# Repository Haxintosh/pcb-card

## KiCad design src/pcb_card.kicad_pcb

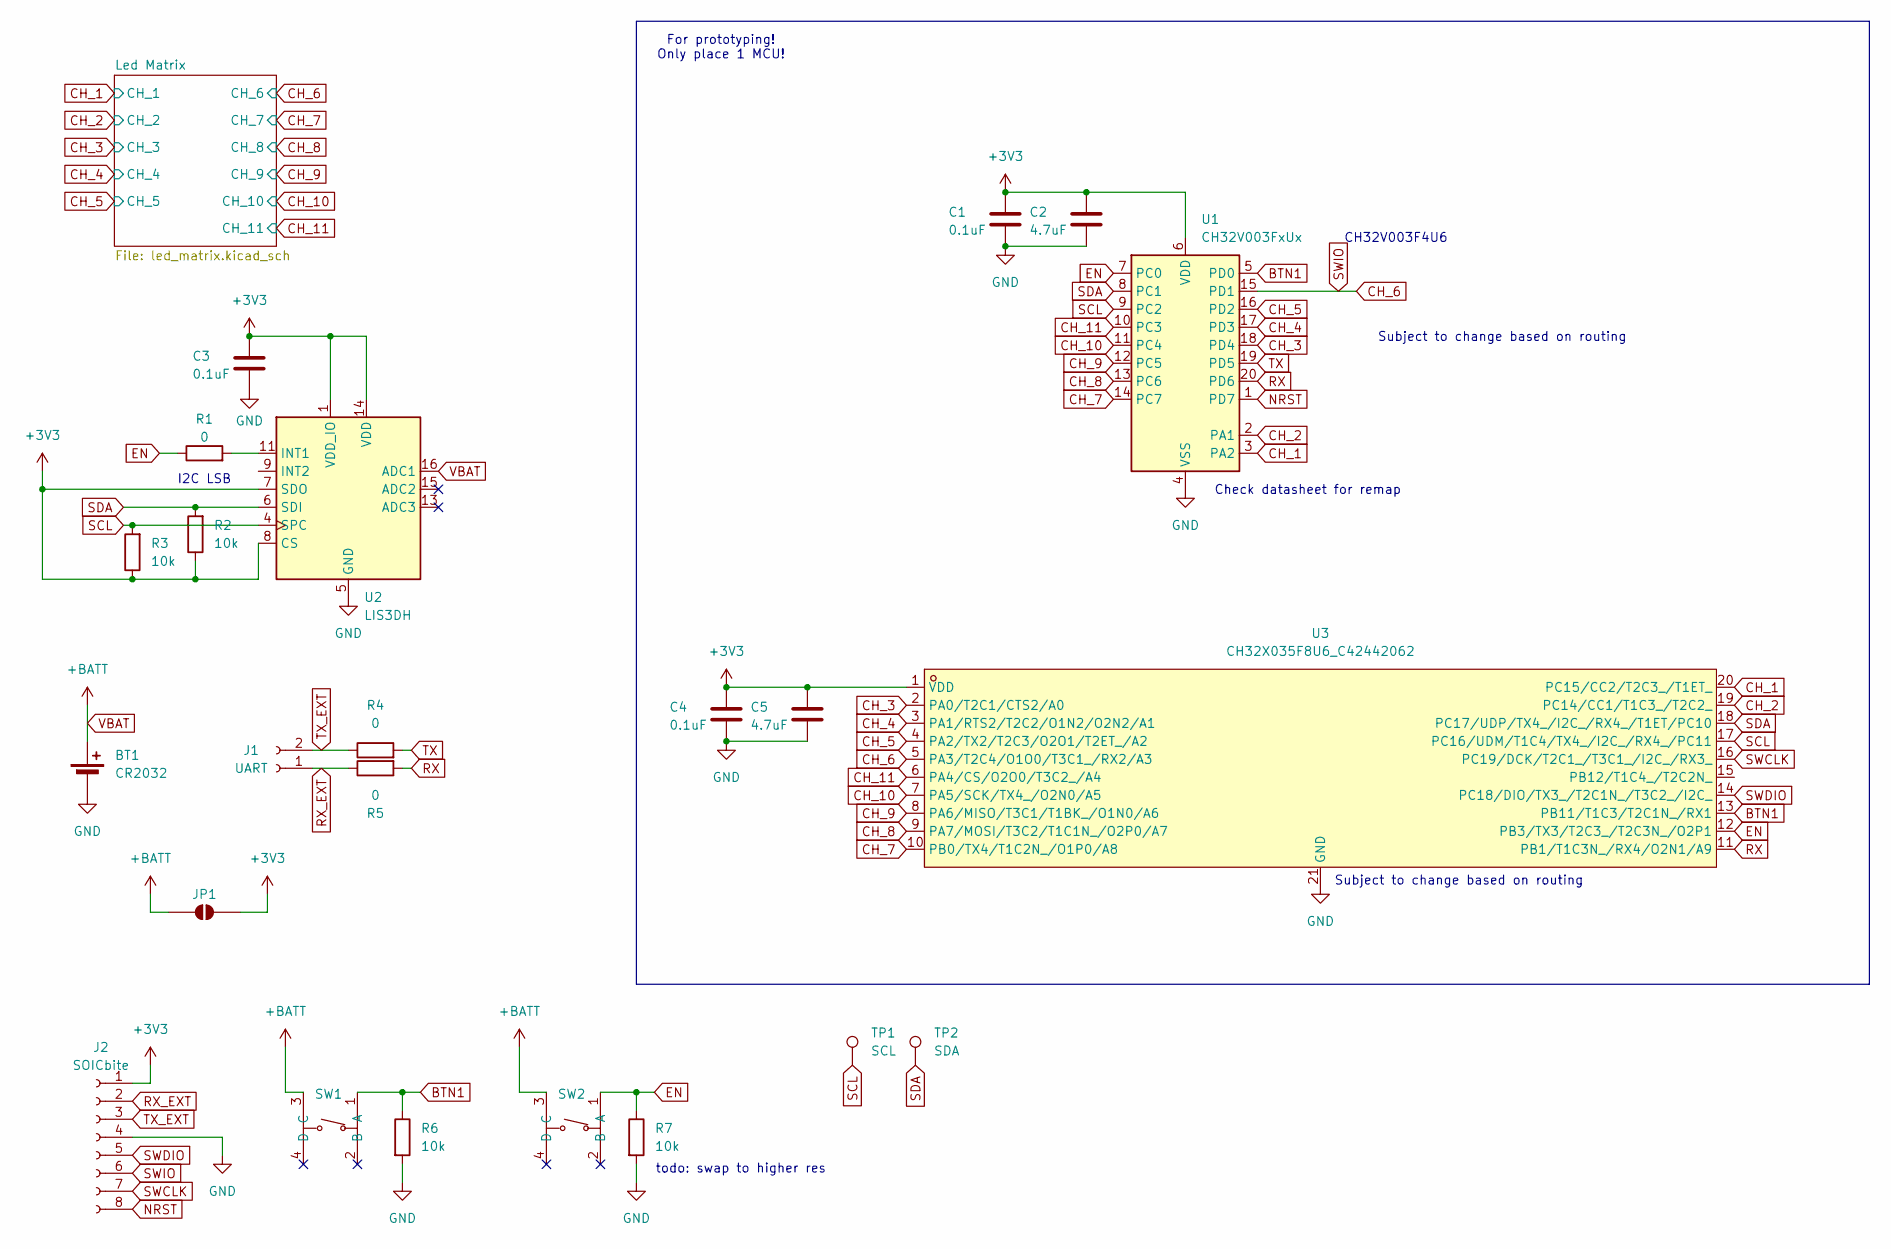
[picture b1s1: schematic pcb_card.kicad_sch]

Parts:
BT1: CR2032; BAT-TH_CR2032-BS-6-1
C1, C3, C4: 0.1uF; C_0603_1608Metric
C2, C5: 4.7uF; C_0603_1608Metric
J1: UART; JST_PH_B2B-PH-K_1x02_P2.00mm_Vertical
J2: SOICbite; SOIC_clipProgSmall
JP1: SolderJumper_2_Open; SolderJumper-2_P1.3mm_Open_TrianglePad1.0x1.5mm
R1, R4, R5: 0; R_0805_2012Metric_Pad1.20x1.40mm_HandSolder
R2, R3, R6, R7: 10k; R_0603_1608Metric
SW1, SW2: TS-1187A-B-A-B; SW-SMD_4P-L5.1-W5.1-P3.70-LS6.5-TL_H1.5; MPN TS-1187A-B-A-B; LCSC Part C318884
TP1: SCL; TestPoint_Pad_D2.0mm
TP2: SDA; TestPoint_Pad_D2.0mm
U1: CH32V003FxUx; QFN-20-1EP_3x3mm_P0.4mm_EP1.65x1.65mm; LCSC C5299908
U2: LIS3DH; LGA-16_3x3mm_P0.5mm_LayoutBorder3x5y
U3: CH32X035F8U6_C42442062; QFN-20-1EP_3x3mm_P0.4mm_EP1.65x1.65mm; MPN CH32X035F8U6; LCSC C42442062

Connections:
+3V3: C1.1, C2.1, C3.1, C4.1, C5.1, J2.1, JP1.2 (B), R2.1, R3.1, U1.6 (VDD), U2.1 (VDD_IO), U2.7 (SDO), U2.8 (CS), U2.14 (VDD), U3.1 (VDD)
BTN1: R6.1, SW1.1 (A), U1.5 (PD0), U3.13 (PB11/T1C3/T2C1N_/RX1)
CH_1: U1.3 (PA2), U3.20 (PC15/CC2/T2C3_/T1ET_); also elsewhere on the board
CH_2: U1.2 (PA1), U3.19 (PC14/CC1/T1C3_/T2C2_); also elsewhere on the board
CH_3: U1.18 (PD4), U3.2 (PA0/T2C1/CTS2/A0); also elsewhere on the board
CH_4: U1.17 (PD3), U3.3 (PA1/RTS2/T2C2/O1N2/O2N2/A1); also elsewhere on the board
CH_5: U1.16 (PD2), U3.4 (PA2/TX2/T2C3/O2O1/T2ET_/A2); also elsewhere on the board
CH_6: J2.6, U1.15 (PD1), U3.5 (PA3/T2C4/O1O0/T3C1_/RX2/A3); also elsewhere on the board
CH_7: U1.14 (PC7), U3.10 (PB0/TX4/T1C2N_/O1P0/A8); also elsewhere on the board
CH_8: U1.13 (PC6), U3.9 (PA7/MOSI/T3C2/T1C1N_/O2P0/A7); also elsewhere on the board
CH_9: U1.12 (PC5), U3.8 (PA6/MISO/T3C1/T1BK_/O1N0/A6); also elsewhere on the board
CH_10: U1.11 (PC4), U3.7 (PA5/SCK/TX4_/O2N0/A5); also elsewhere on the board
CH_11: U1.10 (PC3), U3.6 (PA4/CS/O2O0/T3C2_/A4); also elsewhere on the board
EN: R1.1, R7.1, SW2.1 (A), U1.7 (PC0), U3.12 (PB3/TX3/T2C3_/T2C3N_/O2P1)
GND: BT1.2 (-), C1.2, C2.2, C3.2, C4.2, C5.2, J2.4, R6.2, R7.2, U1.4 (VSS), U1.21 (VSS), U2.5 (GND), U2.10 (GND), U2.12 (GND), U3.21 (GND)
NRST: J2.8, U1.1 (PD7)
unnamed: R1.2, U2.11 (INT1)
RX: R5.2, U1.20 (PD6), U3.11 (PB1/T1C3N_/RX4/O2N1/A9)
RX_EXT: J1.1, J2.2, R5.1
SCL: R3.2, TP1.1 (1_1), U1.9 (PC2), U2.4 (SPC), U3.17 (PC16/UDM/T1C4/TX4_/I2C_/RX4_/PC11)
SDA: R2.2, TP2.1 (1_1), U1.8 (PC1), U2.6 (SDI), U3.18 (PC17/UDP/TX4_/I2C_/RX4_/T1ET/PC10)
SWCLK: J2.7, U3.16 (PC19/DCK/T2C1_/T3C1_/I2C_/RX3_)
SWDIO: J2.5, U3.14 (PC18/DIO/TX3_/T2C1N_/T3C2_/I2C_)
TX: R4.2, U1.19 (PD5)
TX_EXT: J1.2, J2.3, R4.1
VBAT: BT1.1 (+), JP1.1 (A), SW1.3 (C), SW2.3 (C), U2.16 (ADC1)

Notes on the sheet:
todo: swap to higher res
For prototyping! Only place 1 MCU!
Check datasheet for remap
Subject to change based on routing
CH32V003F4U6
I2C LSB

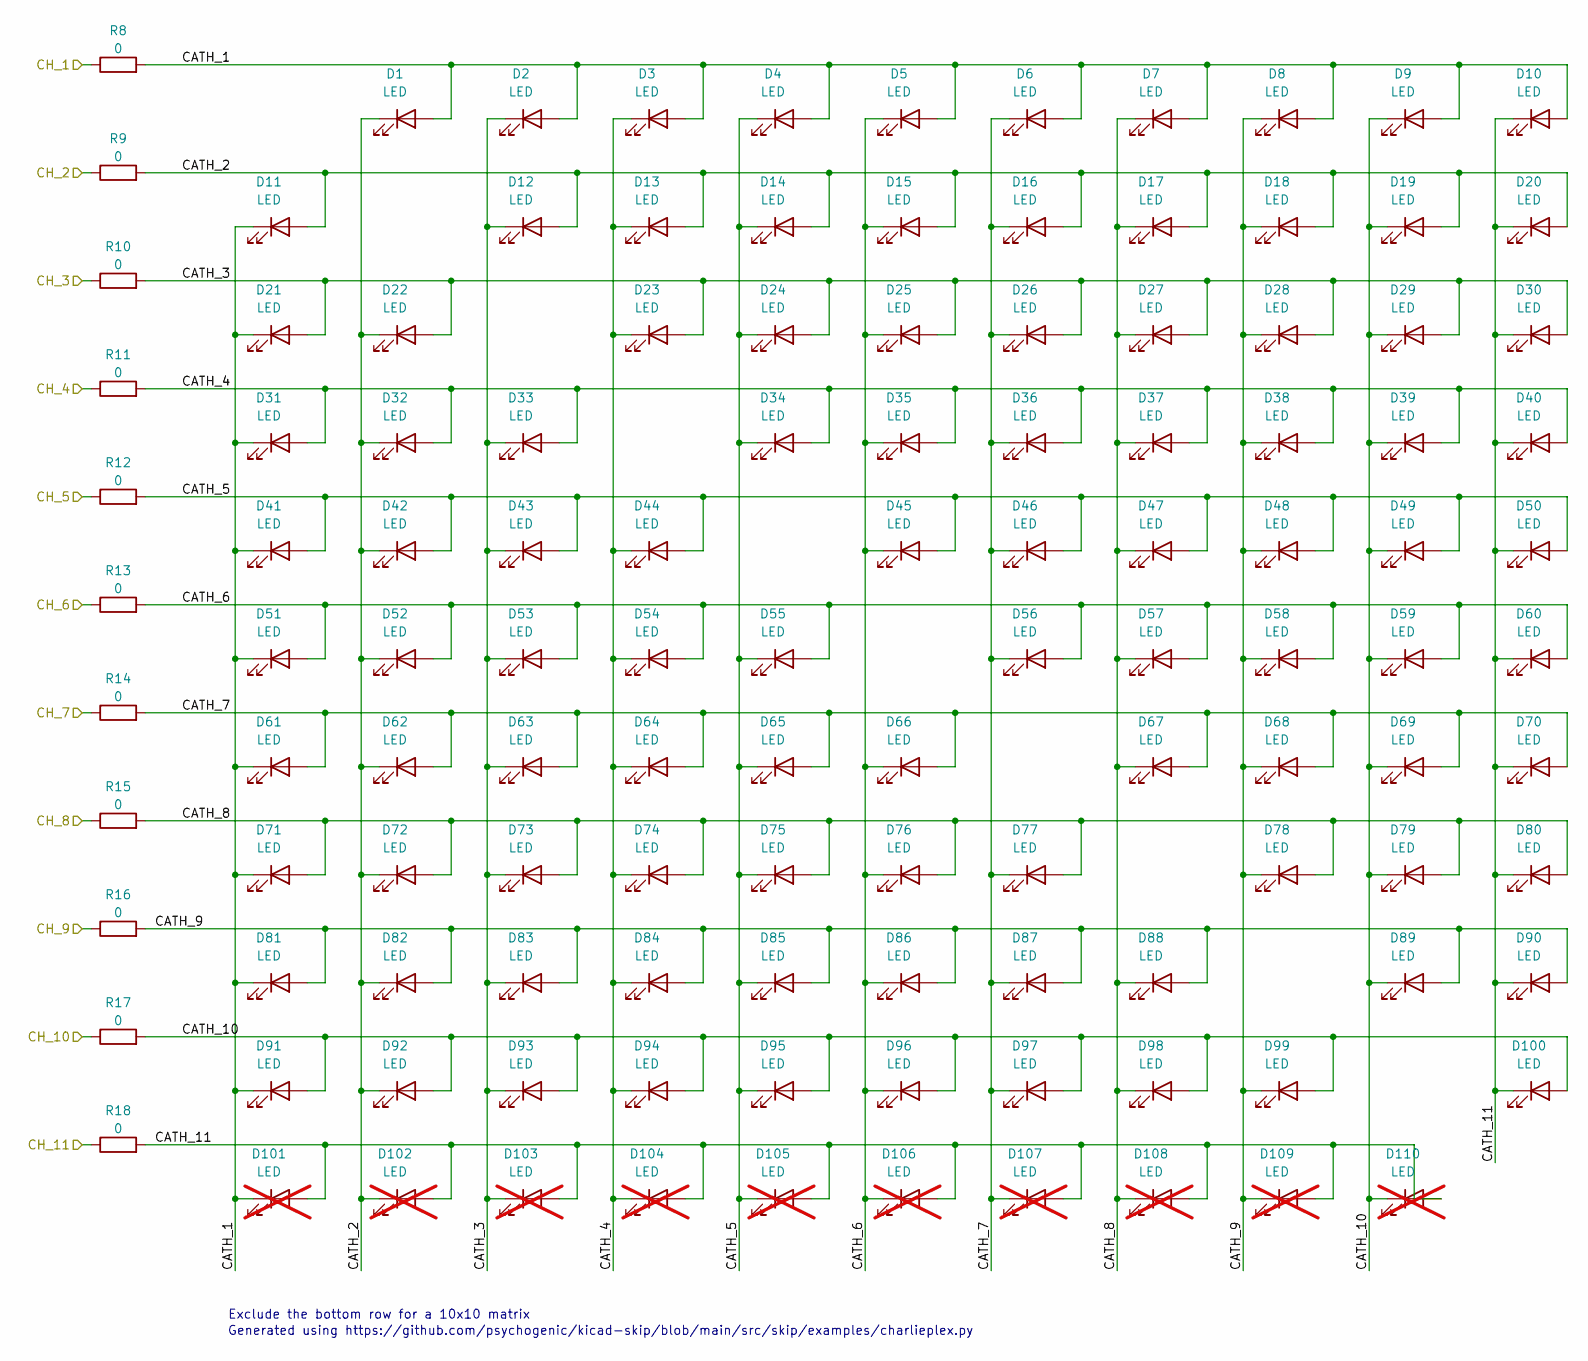
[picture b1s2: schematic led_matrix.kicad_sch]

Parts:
D1, D2, D3, D4, D5, D6, D7, D8, D9, D10, D11, D12, D13, D14, D15, D16, D17, D18, D19, D20, D21, D22, D23, D24, D25, D26, D27, D28, D29, D30, D31, D32, D33, D34, D35, D36, D37, D38, D39, D40, D41, D42, D43, D44, D45, D46, D47, D48, D49, D50, D51, D52, D53, D54, D55, D56, D57, D58, D59, D60, D61, D62, D63, D64, D65, D66, D67, D68, D69, D70, D71, D72, D73, D74, D75, D76, D77, D78, D79, D80, D81, D82, D83, D84, D85, D86, D87, D88, D89, D90, D91, D92, D93, D94, D95, D96, D97, D98, D99, D100: LED; LED_0603_1608Metric
D101, D102, D103, D104, D105, D106, D107, D108, D109, D110: LED; not fitted
R8, R9, R10, R11, R12, R13, R14, R15, R16, R17, R18: 0; R_0805_2012Metric_Pad1.20x1.40mm_HandSolder

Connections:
/Led Matrix/CATH_1: D1.2 (A), D2.2 (A), D3.2 (A), D4.2 (A), D5.2 (A), D6.2 (A), D7.2 (A), D8.2 (A), D9.2 (A), D10.2 (A), D11.1 (K), D21.1 (K), D31.1 (K), D41.1 (K), D51.1 (K), D61.1 (K), D71.1 (K), D81.1 (K), D91.1 (K), D101.1 (K), R8.2
/Led Matrix/CATH_2: D1.1 (K), D11.2 (A), D12.2 (A), D13.2 (A), D14.2 (A), D15.2 (A), D16.2 (A), D17.2 (A), D18.2 (A), D19.2 (A), D20.2 (A), D22.1 (K), D32.1 (K), D42.1 (K), D52.1 (K), D62.1 (K), D72.1 (K), D82.1 (K), D92.1 (K), D102.1 (K), R9.2
/Led Matrix/CATH_3: D2.1 (K), D12.1 (K), D21.2 (A), D22.2 (A), D23.2 (A), D24.2 (A), D25.2 (A), D26.2 (A), D27.2 (A), D28.2 (A), D29.2 (A), D30.2 (A), D33.1 (K), D43.1 (K), D53.1 (K), D63.1 (K), D73.1 (K), D83.1 (K), D93.1 (K), D103.1 (K), R10.2
/Led Matrix/CATH_4: D3.1 (K), D13.1 (K), D23.1 (K), D31.2 (A), D32.2 (A), D33.2 (A), D34.2 (A), D35.2 (A), D36.2 (A), D37.2 (A), D38.2 (A), D39.2 (A), D40.2 (A), D44.1 (K), D54.1 (K), D64.1 (K), D74.1 (K), D84.1 (K), D94.1 (K), D104.1 (K), R11.2
/Led Matrix/CATH_5: D4.1 (K), D14.1 (K), D24.1 (K), D34.1 (K), D41.2 (A), D42.2 (A), D43.2 (A), D44.2 (A), D45.2 (A), D46.2 (A), D47.2 (A), D48.2 (A), D49.2 (A), D50.2 (A), D55.1 (K), D65.1 (K), D75.1 (K), D85.1 (K), D95.1 (K), D105.1 (K), R12.2
/Led Matrix/CATH_6: D5.1 (K), D15.1 (K), D25.1 (K), D35.1 (K), D45.1 (K), D51.2 (A), D52.2 (A), D53.2 (A), D54.2 (A), D55.2 (A), D56.2 (A), D57.2 (A), D58.2 (A), D59.2 (A), D60.2 (A), D66.1 (K), D76.1 (K), D86.1 (K), D96.1 (K), D106.1 (K), R13.2
/Led Matrix/CATH_7: D6.1 (K), D16.1 (K), D26.1 (K), D36.1 (K), D46.1 (K), D56.1 (K), D61.2 (A), D62.2 (A), D63.2 (A), D64.2 (A), D65.2 (A), D66.2 (A), D67.2 (A), D68.2 (A), D69.2 (A), D70.2 (A), D77.1 (K), D87.1 (K), D97.1 (K), D107.1 (K), R14.2
/Led Matrix/CATH_8: D7.1 (K), D17.1 (K), D27.1 (K), D37.1 (K), D47.1 (K), D57.1 (K), D67.1 (K), D71.2 (A), D72.2 (A), D73.2 (A), D74.2 (A), D75.2 (A), D76.2 (A), D77.2 (A), D78.2 (A), D79.2 (A), D80.2 (A), D88.1 (K), D98.1 (K), D108.1 (K), R15.2
/Led Matrix/CATH_9: D8.1 (K), D18.1 (K), D28.1 (K), D38.1 (K), D48.1 (K), D58.1 (K), D68.1 (K), D78.1 (K), D81.2 (A), D82.2 (A), D83.2 (A), D84.2 (A), D85.2 (A), D86.2 (A), D87.2 (A), D88.2 (A), D89.2 (A), D90.2 (A), D99.1 (K), D109.1 (K), R16.2
/Led Matrix/CATH_10: D9.1 (K), D19.1 (K), D29.1 (K), D39.1 (K), D49.1 (K), D59.1 (K), D69.1 (K), D79.1 (K), D89.1 (K), D91.2 (A), D92.2 (A), D93.2 (A), D94.2 (A), D95.2 (A), D96.2 (A), D97.2 (A), D98.2 (A), D99.2 (A), D100.2 (A), D110.1 (K), R17.2
/Led Matrix/CATH_11: D10.1 (K), D20.1 (K), D30.1 (K), D40.1 (K), D50.1 (K), D60.1 (K), D70.1 (K), D80.1 (K), D90.1 (K), D100.1 (K), D101.2 (A), D102.2 (A), D103.2 (A), D104.2 (A), D105.2 (A), D106.2 (A), D107.2 (A), D108.2 (A), D109.2 (A), D110.2 (A), R18.2
CH_1: R8.1; also elsewhere on the board
CH_2: R9.1; also elsewhere on the board
CH_3: R10.1; also elsewhere on the board
CH_4: R11.1; also elsewhere on the board
CH_5: R12.1; also elsewhere on the board
CH_6: R13.1; also elsewhere on the board
CH_7: R14.1; also elsewhere on the board
CH_8: R15.1; also elsewhere on the board
CH_9: R16.1; also elsewhere on the board
CH_10: R17.1; also elsewhere on the board
CH_11: R18.1; also elsewhere on the board

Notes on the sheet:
Generated using https://github.com/psychogenic/kicad-skip/blob/main/src/skip/examples/charlieplex.py
Exclude the bottom row for a 10x10 matrix

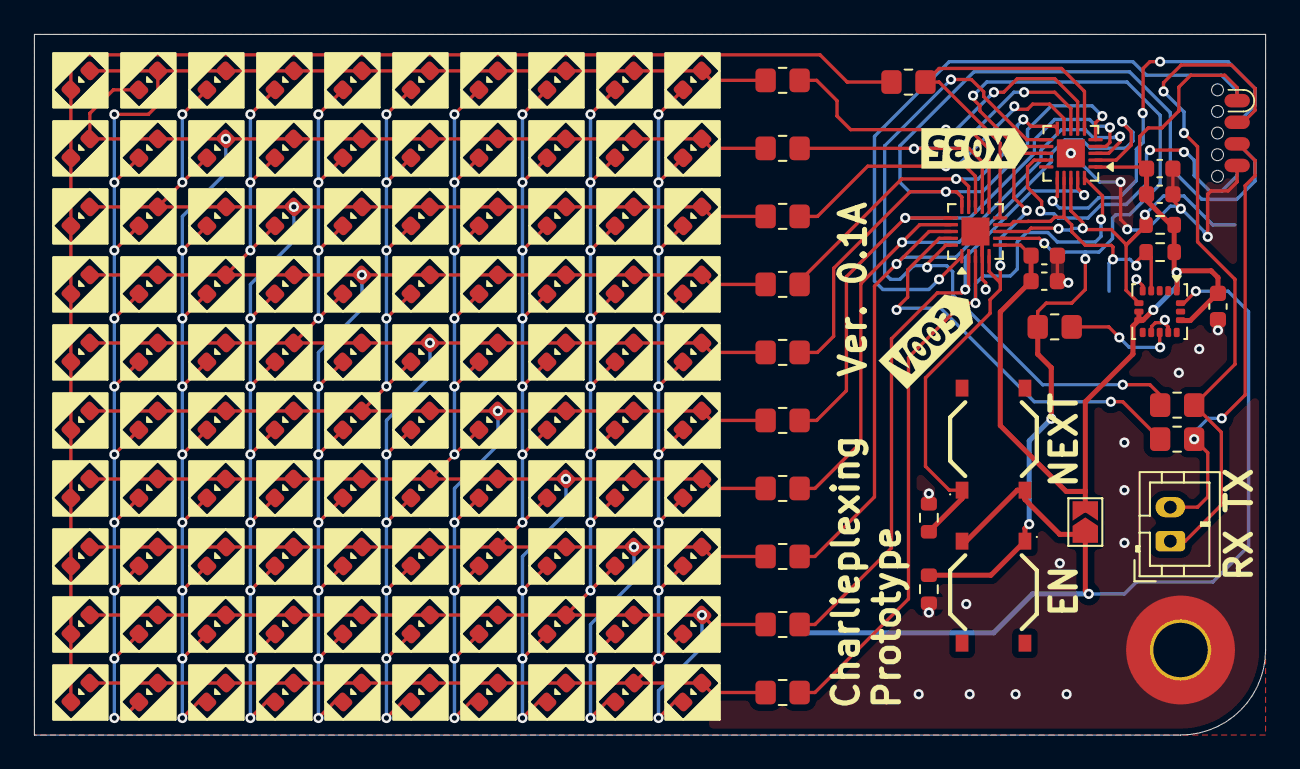
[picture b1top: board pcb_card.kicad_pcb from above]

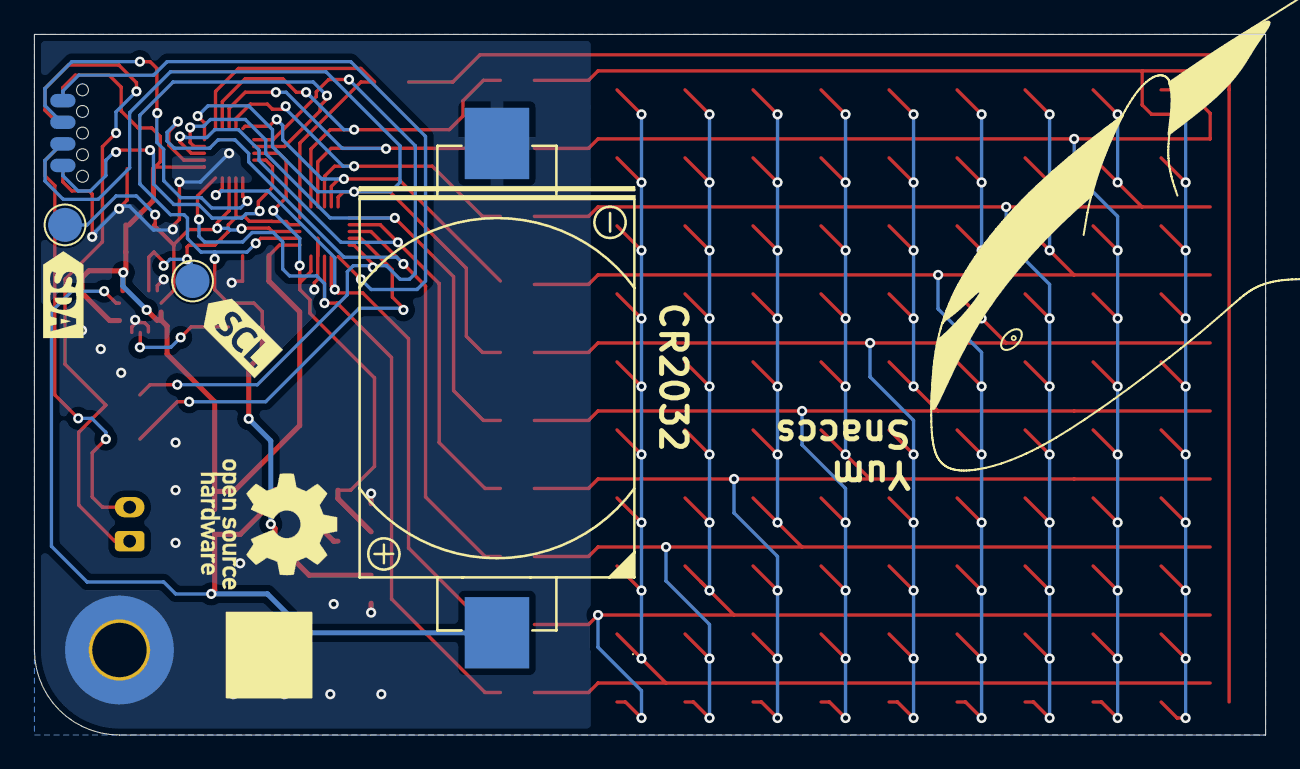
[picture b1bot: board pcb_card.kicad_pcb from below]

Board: 2 copper layers, 72.4 x 41.2 mm, 138 parts (5 on the bottom side), 37 nets.

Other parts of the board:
kibuzzard-6A21B8D0: G***; kibuzzard-6A21B8D0
kibuzzard-6A21B803: G***; kibuzzard-6A21B803
kibuzzard-6A30280D: G***; kibuzzard-6A30280D
kibuzzard-6A302872: G***; kibuzzard-6A302872

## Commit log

2026-05-17 chore: add licence
    Added CERN OHL v2 permissive
2026-05-25 chore: init kicad project
2026-05-25 chore: update project file structure
2026-06-03 feat: prototype schematic
2026-06-05 feat: prototype PCB done
2026-06-15 chore: breaks out I2C pins
2026-06-18 chore: basic platformio setup + js prototyping
